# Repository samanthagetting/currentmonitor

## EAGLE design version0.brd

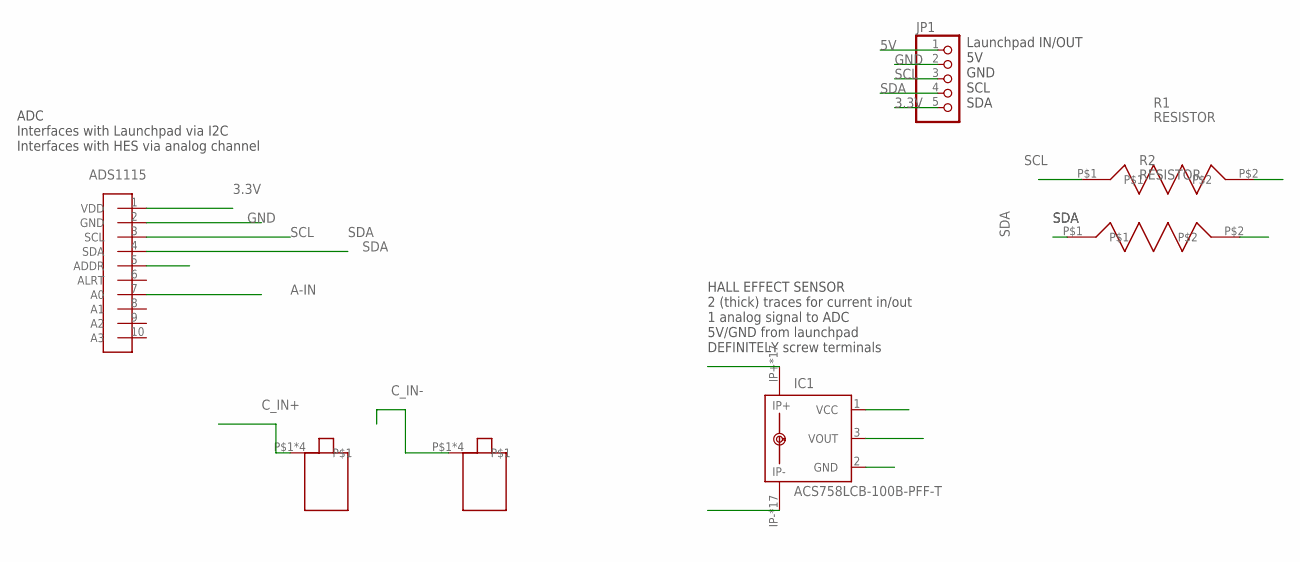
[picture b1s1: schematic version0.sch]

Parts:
ADC_JUMPER: ADS1115-BREAKOUTBOARD; 1X10
IC1: ACS758LCB-100B-PFF-T; CB-PFF
JP1: PINHD-1X5; 1X05
R1, R2: RESISTOR; 0805
U$5, U$6: SCREW_TERM_50A

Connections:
3.3V: ADC_JUMPER.1 (VDD), JP1.5, R1.P$2, R2.P$2
5V: IC1.1 (VCC), JP1.1
A-IN: ADC_JUMPER.7 (A0), IC1.3 (VOUT)
C_IN+: IC1.IP+, IC1.IP+@2 (IP+), IC1.IP+@3 (IP+), IC1.IP+@4 (IP+), IC1.IP+@5 (IP+), IC1.IP+@6 (IP+), IC1.IP+@7 (IP+), IC1.IP+@8 (IP+), IC1.IP+@9 (IP+), IC1.IP+@10 (IP+), IC1.IP+@11 (IP+), IC1.IP+@12 (IP+), IC1.IP+@13 (IP+), IC1.IP+@14 (IP+), IC1.IP+@15 (IP+), IC1.IP+@16 (IP+), IC1.IP+@17 (IP+), U$5.P$1, U$5.P$2, U$5.P$3, U$5.P$4
C_IN-: IC1.IP-, IC1.IP-@2 (IP-), IC1.IP-@3 (IP-), IC1.IP-@4 (IP-), IC1.IP-@5 (IP-), IC1.IP-@6 (IP-), IC1.IP-@7 (IP-), IC1.IP-@8 (IP-), IC1.IP-@9 (IP-), IC1.IP-@10 (IP-), IC1.IP-@11 (IP-), IC1.IP-@12 (IP-), IC1.IP-@13 (IP-), IC1.IP-@14 (IP-), IC1.IP-@15 (IP-), IC1.IP-@16 (IP-), IC1.IP-@17 (IP-), U$6.P$1, U$6.P$2, U$6.P$3, U$6.P$4
GND: ADC_JUMPER.2 (GND), ADC_JUMPER.5 (ADDR), IC1.2 (GND), JP1.2
SCL: ADC_JUMPER.3 (SCL), JP1.3, R1.P$1
SDA: ADC_JUMPER.4 (SDA), JP1.4, R2.P$1

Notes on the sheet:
ADC Interfaces with Launchpad via I2C Interfaces with HES via analog channel
Launchpad IN/OUT 5V GND SCL SDA
HALL EFFECT SENSOR 2 (thick) traces for current in/out 1 analog signal to ADC 5V/GND from launchpad DEFINITELY screw terminals

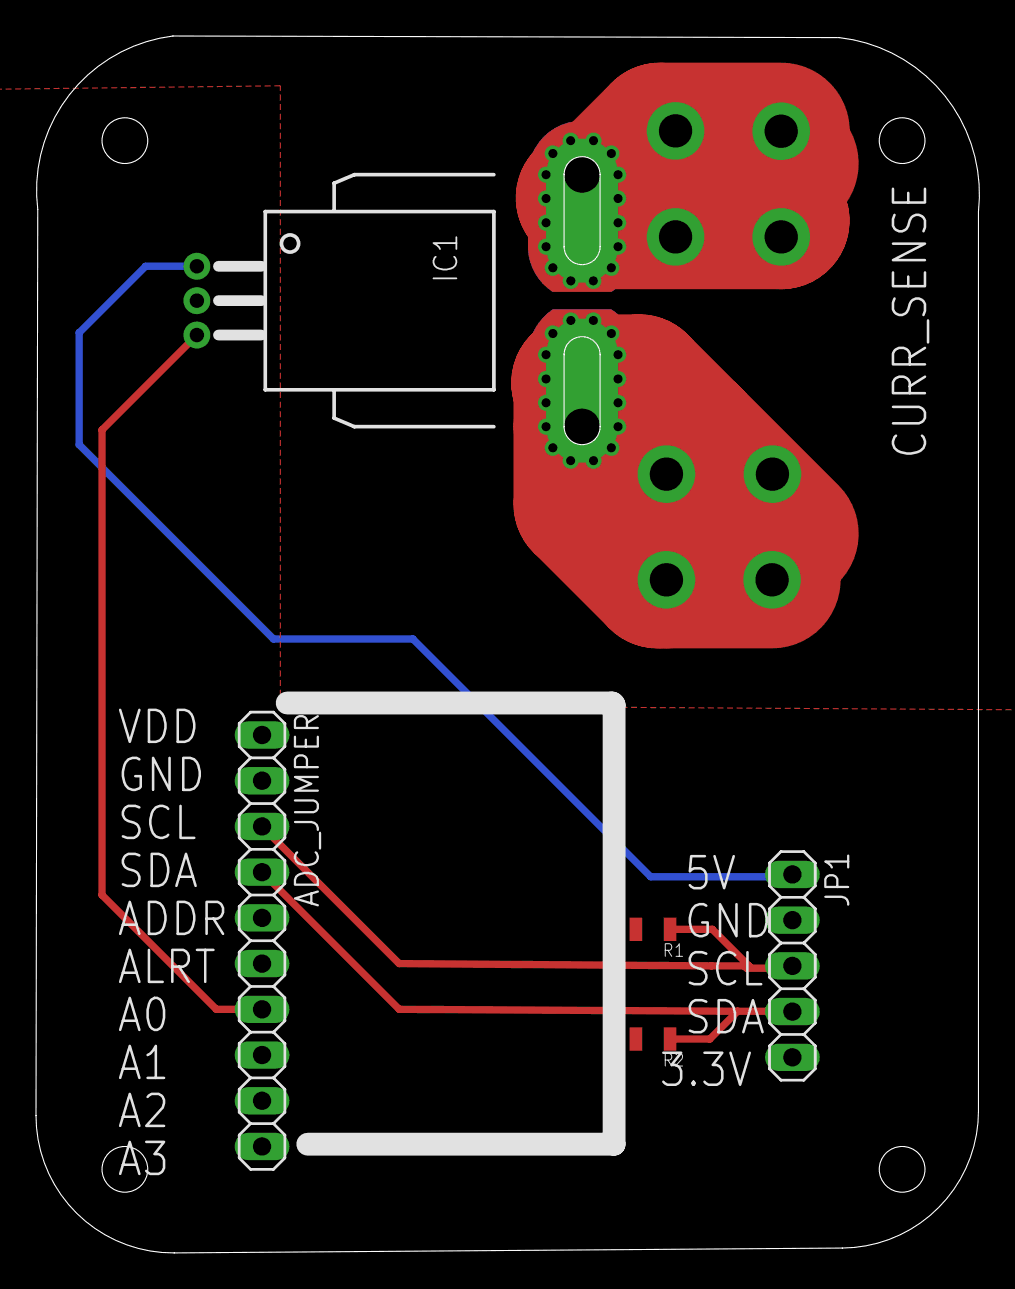
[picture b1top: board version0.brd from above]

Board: 2 copper layers, 52.4 x 67.6 mm, 7 parts (0 on the bottom side), 8 nets.

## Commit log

2018-01-22 added files
